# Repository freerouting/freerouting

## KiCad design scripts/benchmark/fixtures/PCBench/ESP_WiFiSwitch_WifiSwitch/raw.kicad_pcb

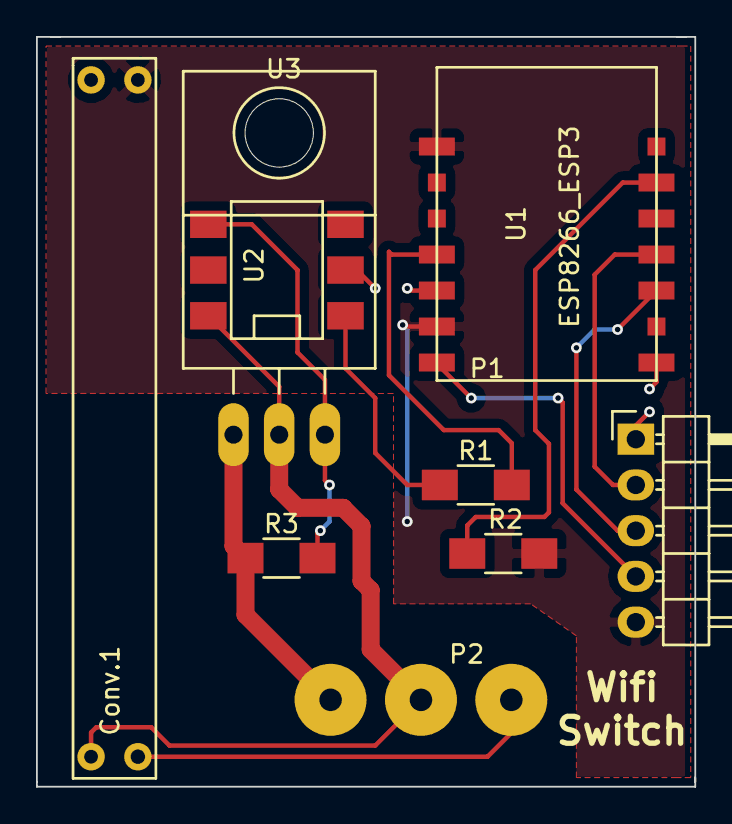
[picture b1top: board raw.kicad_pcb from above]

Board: 2 copper layers, 36.6 x 41.7 mm, 9 parts (0 on the bottom side), 12 nets.

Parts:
Conv.1: AC to DC convertor 3V3; AC_DC_Conv
P1: CONN_01X05; Pin_Header_Angled_1x05
P2: CONN_01X03; WirePad_3x-5mmDrill
R1: 220R; R_1206_HandSoldering
R2: 4K7; R_1206_HandSoldering
R3: 330R; R_1206_HandSoldering
U1: ESP8266_ESP3; ESP8266-ESP-03
U2: MOC3031S; DIP-6_SMD
U3: TRIAC; TO-220_Neutral123_Horizontal_LargePads

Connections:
+3V3: Conv.1.1, P1.5, R2.2, U1.8, U1.13
GND: Conv.1.2, P1.1, U1.1, U1.12, U2.2
unnamed: Conv.1.3, P2.3
unnamed: Conv.1.4, P2.2, U2.6, U3.2
unnamed: P1.2, U1.4
unnamed: P1.3, U1.3
unnamed: P1.4, U1.14
unnamed: P2.1, R3.2, U3.1
unnamed: R1.1, U2.1
unnamed: R1.2, U1.11
unnamed: R2.1, U1.6
unnamed: R3.1, U2.4, U3.3

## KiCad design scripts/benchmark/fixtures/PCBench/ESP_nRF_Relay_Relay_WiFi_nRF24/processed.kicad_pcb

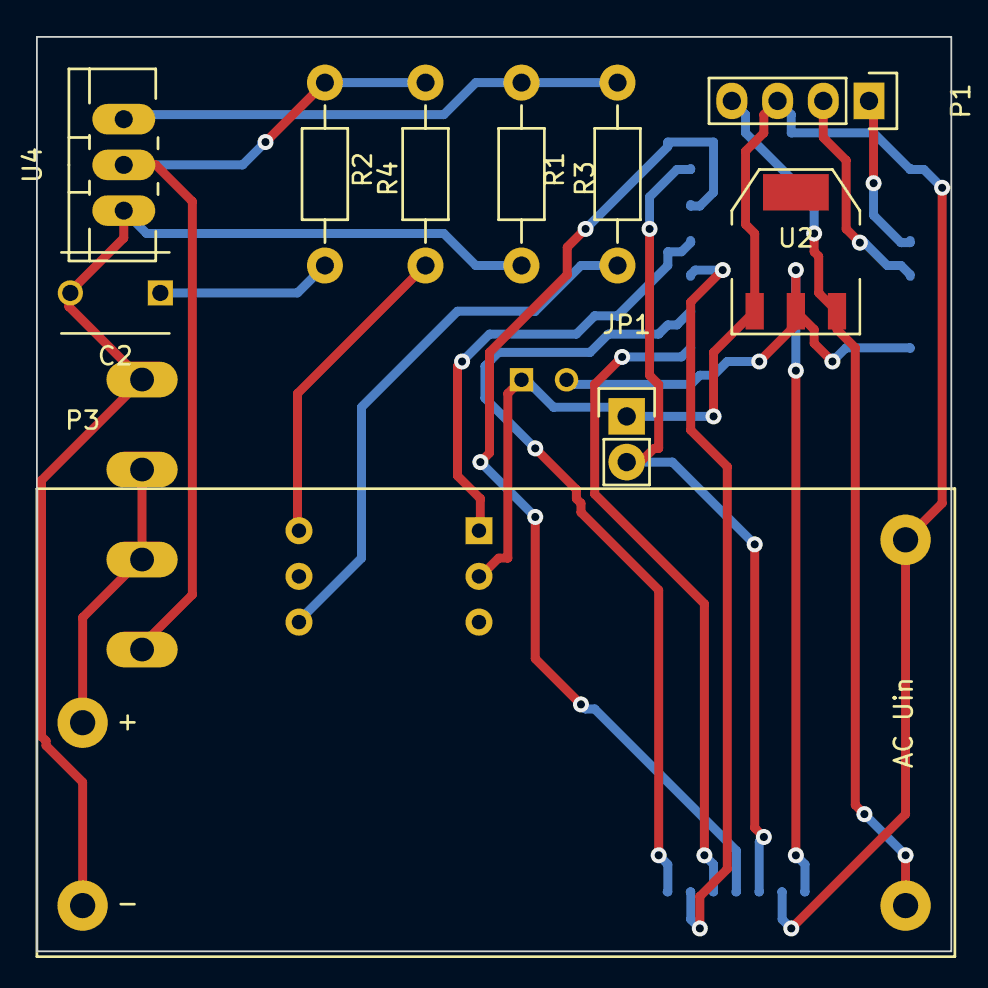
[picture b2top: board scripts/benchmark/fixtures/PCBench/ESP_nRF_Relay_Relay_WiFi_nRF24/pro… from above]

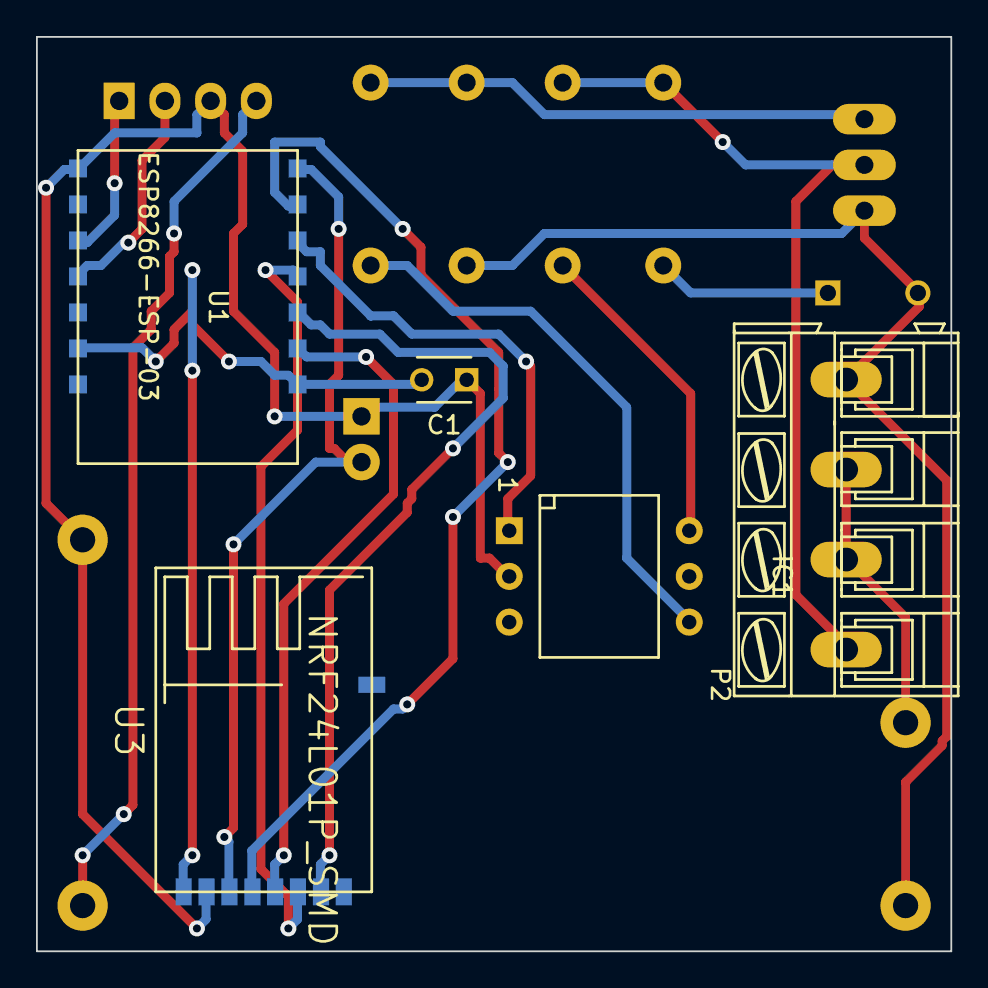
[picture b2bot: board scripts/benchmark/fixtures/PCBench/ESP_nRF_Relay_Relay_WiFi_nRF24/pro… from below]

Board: 2 copper layers, 50.8 x 50.8 mm, 15 parts (5 on the bottom side), 18 nets.

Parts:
C1: 0.01; C_Disc_D3_P2.5
C2: 10n; C_Disc_D6_P5
IC1: MOC3061M; Optocoupler_6pin_wide_Stile-II
JP1: JUMPER; Pin_Header_Straight_1x02
P1: CONN_4; Pin_Header_Straight_1x04
P2: CONN_4; AK300-4
P3: CONN_01X04; ACDC-Converter_TRACO-TMLM-05
R1, R2, R3, R4: 360; Resistor_Horizontal_RM10mm
U1: ESP8266-ESP-03
U2: NCP1117ST33T3G; SOT-223
U3: NRF24L01P_SMD
U4: TRIAC; TO-220_Neutral123_Vertical_LargePads

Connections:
GND: C1.1, IC1.2, JP1.1, P1.3, P3.4, U1.1, U2.1, U3.2
unnamed: C1.2, U1.6, U1.8, U2.2, U3.1
unnamed: C2.1, R4.2
unnamed: C2.2, P2.4, P3.2, R3.2, U4.1
unnamed: IC1.1, U1.12
unnamed: IC1.4, R1.1
unnamed: IC1.6, R2.1
unnamed: JP1.2, U1.14, U3.3
unnamed: P1.1, U1.3
unnamed: P1.2, U1.4
unnamed: P2.1, R2.2, R4.1, U4.2
unnamed: P2.2, P2.3, P3.1
unnamed: R1.2, R3.1, U4.3
unnamed: U1.9, U3.5
unnamed: U1.10, U3.7
unnamed: U1.11, U3.6
unnamed: U1.13, U3.4
VCC: P1.4, P3.3, U2.3

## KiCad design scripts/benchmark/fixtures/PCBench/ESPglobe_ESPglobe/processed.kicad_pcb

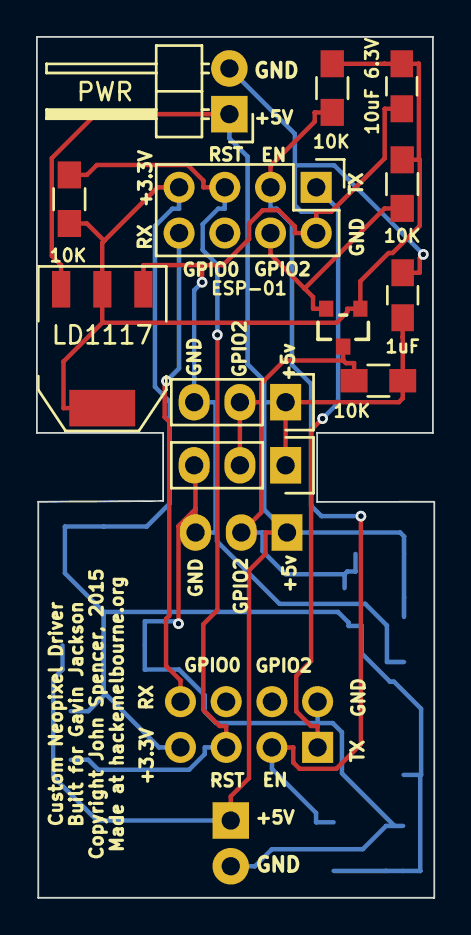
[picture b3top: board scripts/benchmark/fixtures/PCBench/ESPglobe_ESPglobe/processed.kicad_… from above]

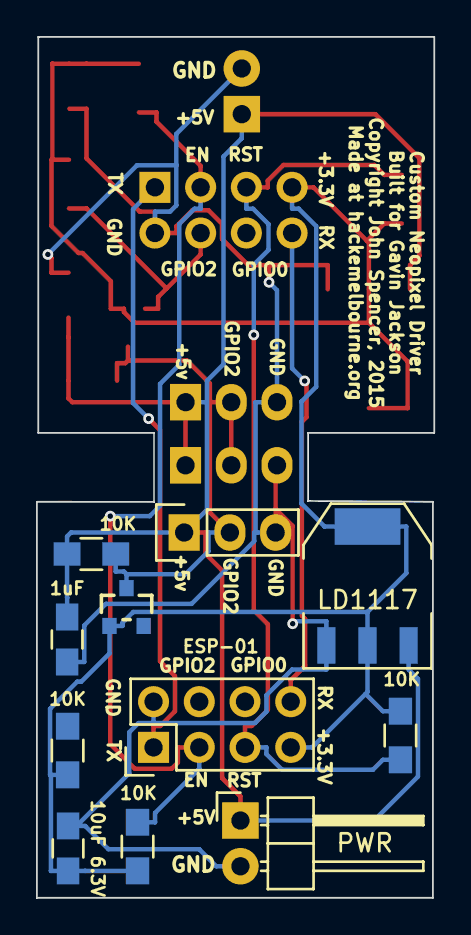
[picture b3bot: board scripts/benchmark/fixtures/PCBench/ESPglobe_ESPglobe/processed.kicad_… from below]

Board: 2 copper layers, 22.1 x 47.8 mm, 22 parts (11 on the bottom side), 9 nets.

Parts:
 P1,  P11: NEOPIXEL; Pin_Header_Straight_1x03
C1, C11: 1uF; C_0805_HandSoldering
C2, C21: 10uF 6.3V; C_0805_HandSoldering
P3, P31: PWR; Pin_Header_Angled_1x02
Q1, Q11: 2n7002; SOT23_FET
R1, R2, R3, R4, R11, R21, R31, R41: 10K; R_0805_HandSoldering
U1, U11: LD1117; SOT-223
U2, U21: ESP-01; Pin_Header_Straight_2x04

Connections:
+3V3: C2.1, C21.1, Q1.G, Q11.G, R1.2, R2.2, R4.1, R11.2, R21.2, R41.1, U1.2, U1.4, U2.7, U11.2, U11.4, U21.7
+5V: P1.1, P11.1, C1.1, C11.1, P3.1, P31.1, R3.1, R31.1, U1.3, U11.3
GND: P1.3, P11.3, C1.2, C2.2, C11.2, C21.2, P3.2, P31.2, U1.1, U2.2, U11.1, U21.2
GPIO2: Q11.S, R41.2, U21.4
NEO: P1.2, P11.2, Q1.D, Q11.D, R3.2, R31.2
unnamed: R1.1, R11.1, U2.5, U21.5
unnamed: R2.1, R21.1, U2.3, U21.3
RX: U2.8, U21.8
TX: U2.1, U21.1

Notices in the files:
scripts/benchmark/fixtures/PCBench/ESPglobe_ESPglobe/processed.kicad_pcb:
Copyright John Spencer, 2015
